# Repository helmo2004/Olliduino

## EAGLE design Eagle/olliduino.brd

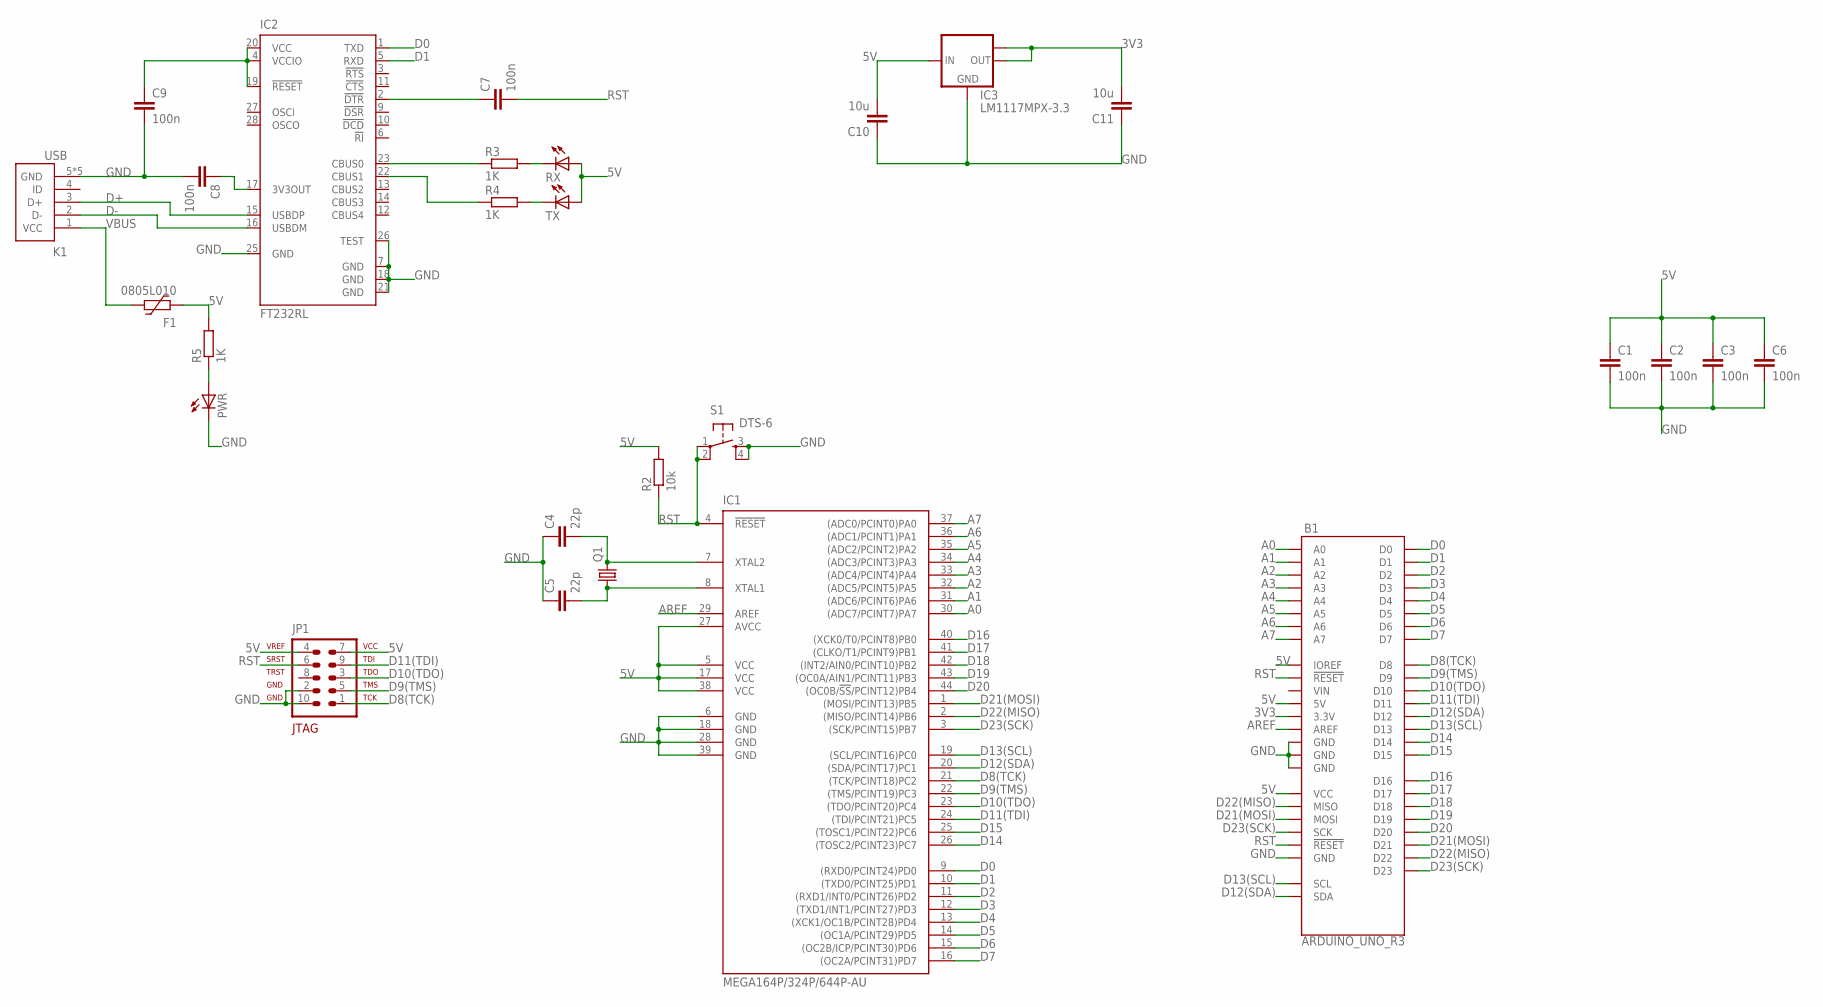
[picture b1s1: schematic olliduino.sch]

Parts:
B1: ARDUINO_UNO_R3; ARDUINO_R3
C1, C2, C3, C6, C7, C8, C9: 100n; C0805
C4, C5: 22p; C0805
C10, C11: 10u; C0805
F1: 0805L010; 0805L
IC1: MEGA164P/324P/644P-AU; TQFP44
IC2: FT232RL; SSOP28
IC3: LM1117MPX-3.3; SOT223
JP1: AVR-JTAG-10
K1: USB; 651005136521
PWR: LEDCHIPLED_0805; CHIPLED_0805
Q1: CRYSTALHC49U-V; HC49U-V
R2: 10k; M0805
R3, R4, R5: 1K; M0805
RX: LEDCHIPLED_0805; CHIPLED_0805
S1: DTS-6
TX: LEDCHIPLED_0805; CHIPLED_0805

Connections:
3V3: B1.3.3V, C11.2, IC3.2 (OUT), IC3.TAB (OUT1)
5V: B1.5V, B1.IOREF, B1.VCC, C1.1, C2.1, C3.1, C6.1, C9.1, C10.2, F1.2, IC1.5 (VCC), IC1.17 (VCC), IC1.27 (AVCC), IC1.38 (VCC), IC2.4 (VCCIO), IC2.19 (!RESET), IC2.20 (VCC), IC3.3 (IN), JP1.4, JP1.7, R2.2, R5.2, RX.A, TX.A
A0: B1.A0, IC1.30 ((ADC7/PCINT7)PA7)
A1: B1.A1, IC1.31 ((ADC6/PCINT6)PA6)
A2: B1.A2, IC1.32 ((ADC5/PCINT5)PA5)
A3: B1.A3, IC1.33 ((ADC4/PCINT4)PA4)
A4: B1.A4, IC1.34 ((ADC3/PCINT3)PA3)
A5: B1.A5, IC1.35 ((ADC2/PCINT2)PA2)
A6: B1.A6, IC1.36 ((ADC1/PCINT1)PA1)
A7: B1.A7, IC1.37 ((ADC0/PCINT0)PA0)
AREF: B1.AREF, IC1.29 (AREF)
D0: B1.D0, IC1.9 ((RXD0/PCINT24)PD0), IC2.1 (TXD)
D1: B1.D1, IC1.10 ((TXD0/PCINT25)PD1), IC2.5 (RXD)
D2: B1.D2, IC1.11 ((RXD1/INT0/PCINT26)PD2)
D3: B1.D3, IC1.12 ((TXD1/INT1/PCINT27)PD3)
D4: B1.D4, IC1.13 ((XCK1/OC1B/PCINT28)PD4)
D5: B1.D5, IC1.14 ((OC1A/PCINT29)PD5)
D6: B1.D6, IC1.15 ((OC2B/ICP/PCINT30)PD6)
D7: B1.D7, IC1.16 ((OC2A/PCINT31)PD7)
D8(TCK): B1.D8, IC1.21 ((TCK/PCINT18)PC2), JP1.1
D9(TMS): B1.D9, IC1.22 ((TMS/PCINT19)PC3), JP1.5
D10(TDO): B1.D10, IC1.23 ((TDO/PCINT20)PC4), JP1.3
D11(TDI): B1.D11, IC1.24 ((TDI/PCINT21)PC5), JP1.9
D12(SDA): B1.D12, B1.SDA, IC1.20 ((SDA/PCINT17)PC1)
D13(SCL): B1.D13, B1.SCL, IC1.19 ((SCL/PCINT16)PC0)
D14: B1.D14, IC1.26 ((TOSC2/PCINT23)PC7)
D15: B1.D15, IC1.25 ((TOSC1/PCINT22)PC6)
D16: B1.D16, IC1.40 ((XCK0/T0/PCINT8)PB0)
D17: B1.D17, IC1.41 ((CLKO/T1/PCINT9)PB1)
D18: B1.D18, IC1.42 ((INT2/AIN0/PCINT10)PB2)
D19: B1.D19, IC1.43 ((OC0A/AIN1/PCINT11)PB3)
D20: B1.D20, IC1.44 ((OC0B/!SS!/PCINT12)PB4)
D21(MOSI): B1.D21, B1.MOSI, IC1.1 ((MOSI/PCINT13)PB5)
D22(MISO): B1.D22, B1.MISO, IC1.2 ((MISO/PCINT14)PB6)
D23(SCK): B1.D23, B1.SCK, IC1.3 ((SCK/PCINT15)PB7)
D+: IC2.15 (USBDP), K1.3 (D+)
D-: IC2.16 (USBDM), K1.2 (D-)
GND: B1.GND@1 (GND), B1.GND@2 (GND), B1.GND@3 (GND), B1.GND@4 (GND), C1.2, C2.2, C3.2, C4.1, C5.1, C6.2, C8.2, C9.2, C10.1, C11.1, IC1.6 (GND), IC1.18 (GND), IC1.28 (GND), IC1.39 (GND), IC2.7 (GND), IC2.18 (GND), IC2.21 (GND), IC2.25 (GND), IC2.26 (TEST), IC3.1 (GND), JP1.2, JP1.10, K1.5 (GND), K1.6 (GND), K1.7 (GND), K1.8 (GND), K1.9 (GND), PWR.C, S1.3, S1.4
unnamed: C4.2, IC1.7 (XTAL2), Q1.2
unnamed: C5.2, IC1.8 (XTAL1), Q1.1
unnamed: R3.2, RX.C
unnamed: R4.2, TX.C
unnamed: C7.1, IC2.2 (!DTR)
unnamed: C8.1, IC2.17 (3V3OUT)
unnamed: PWR.A, R5.1
RST: B1.RESET@1 (!RESET!), B1.RESET@2 (!RESET!), C7.2, IC1.4 (!RESET), JP1.6, R2.1, S1.1, S1.2
RXLED: IC2.23 (CBUS0), R3.1
TXLED: IC2.22 (CBUS1), R4.1
VBUS: F1.1, K1.1 (VCC)

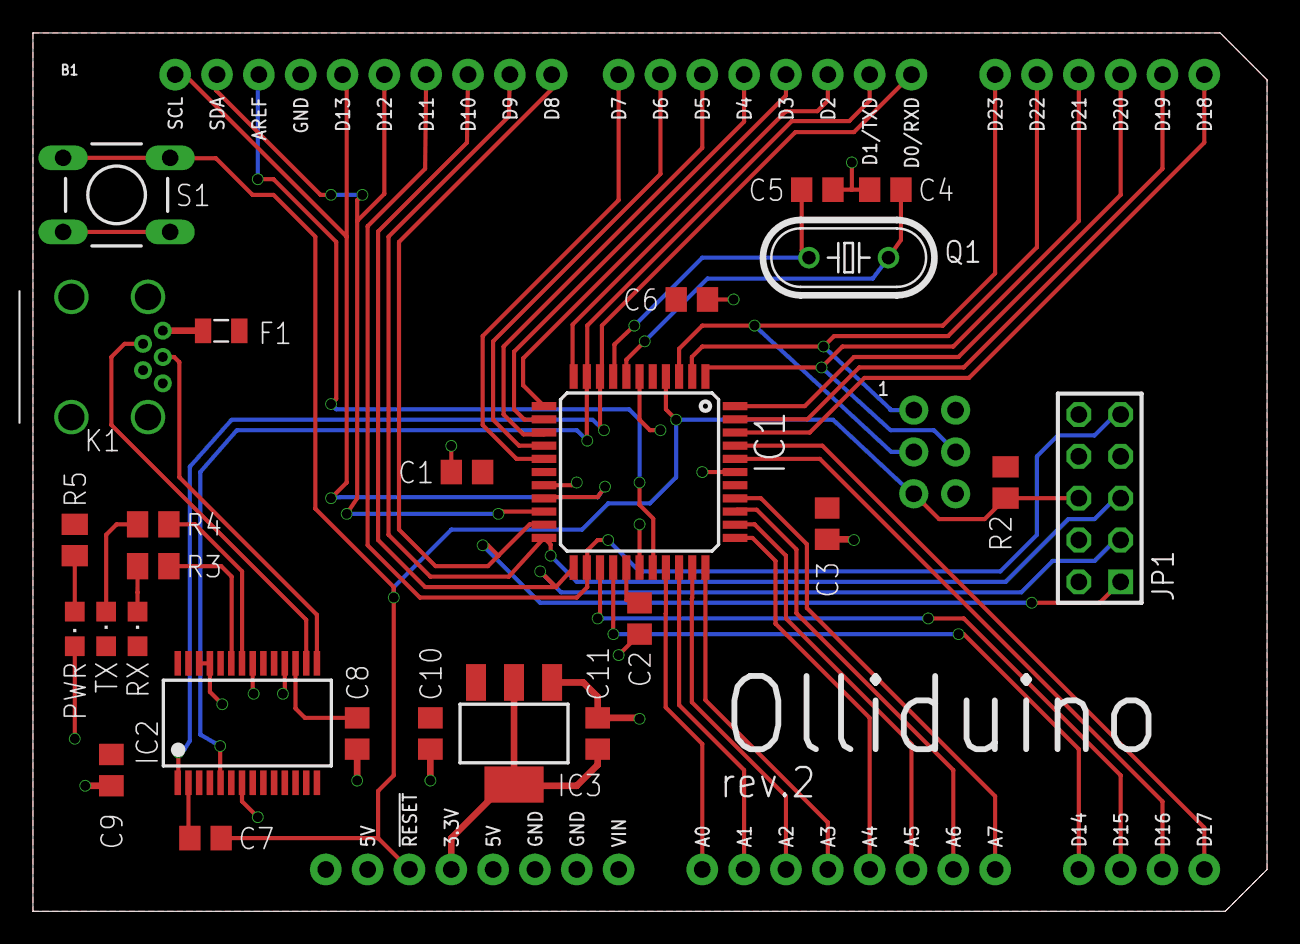
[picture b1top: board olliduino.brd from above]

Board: 2 copper layers, 74.9 x 53.3 mm, 27 parts (0 on the bottom side), 49 nets.

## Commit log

2017-08-09 Add Eagle Stuff
